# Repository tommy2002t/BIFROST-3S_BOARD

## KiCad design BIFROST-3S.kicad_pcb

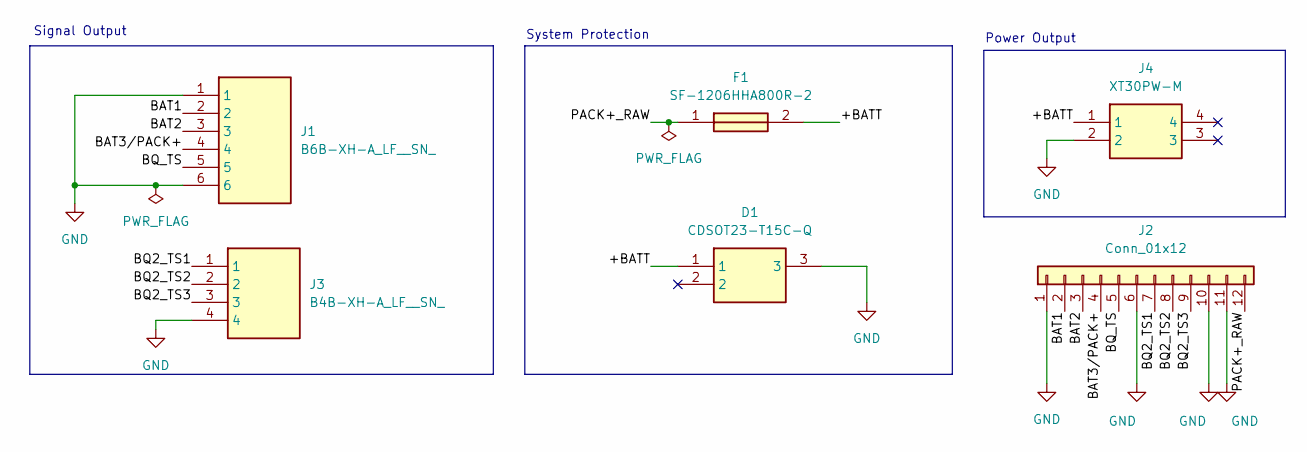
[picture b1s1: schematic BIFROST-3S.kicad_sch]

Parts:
D1: CDSOT23-T15C-Q; SOT95P230X117-3N; Mouser Part Number 652-CDSOT23-T15C-Q
F1: SF-1206HHA800R-2; SF1206HHA800R2; Mouser Part Number 652-SF-1206HHA800R-2
J1: B6B-XH-A_LF__SN_; SHDR6W64P0X250_1X6_1740X575X700P; Mouser Part Number 306-B6BXHALFSN
J2: Conn_01x12; Bifrost_Wire_Pads
J3: B4B-XH-A_LF__SN_; B4BXHALFSN; Mouser Part Number 306-B4BXHALFSN
J4: XT30PW-M; XT30PWM; Manufacturer_Part_Number XT30PW-M

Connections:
/+BATT: D1.1, F1.2, J4.1
/BAT1: J1.2, J2.2
/BAT2: J1.3, J2.3
/BAT3/PACK+: J1.4, J2.4
/BQ2_TS1: J2.7, J3.1
/BQ2_TS2: J2.8, J3.2
/BQ2_TS3: J2.9, J3.3
/BQ_TS: J1.5, J2.5
/PACK+_RAW: F1.1, J2.12
GND: D1.3, J1.1, J1.6, J2.1, J2.6, J2.10, J2.11, J3.4, J4.2

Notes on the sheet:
Power Output
System Protection
Signal Output

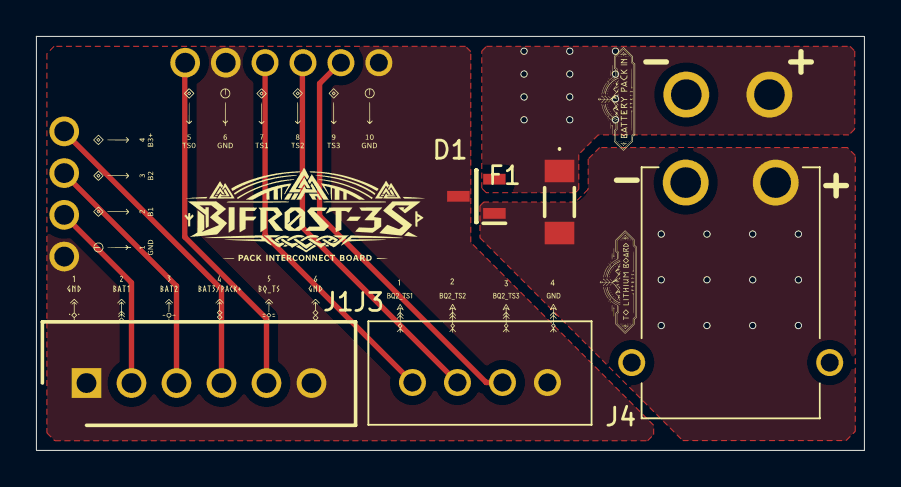
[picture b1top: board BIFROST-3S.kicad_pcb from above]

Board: 4 copper layers, 46.0 x 23.0 mm, 6 parts (0 on the bottom side), 10 nets.
